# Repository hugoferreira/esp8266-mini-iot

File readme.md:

ESP8266 07/12 breakout with one Integrated Voltage Regulator (SPX3819M5-L-3-3) for 3v3 (500mA) and LEDs for Power, RX, TX and Charging.
It has a solder jump to connect GPIO16 with RST in order to enable deep sleep.
It also has an integrated LiPo charger (MCP73831), and a Mini-USB port for charging and direct programming through an integrated FTL232RL.

This is a **work in progress** so use at your own risk.

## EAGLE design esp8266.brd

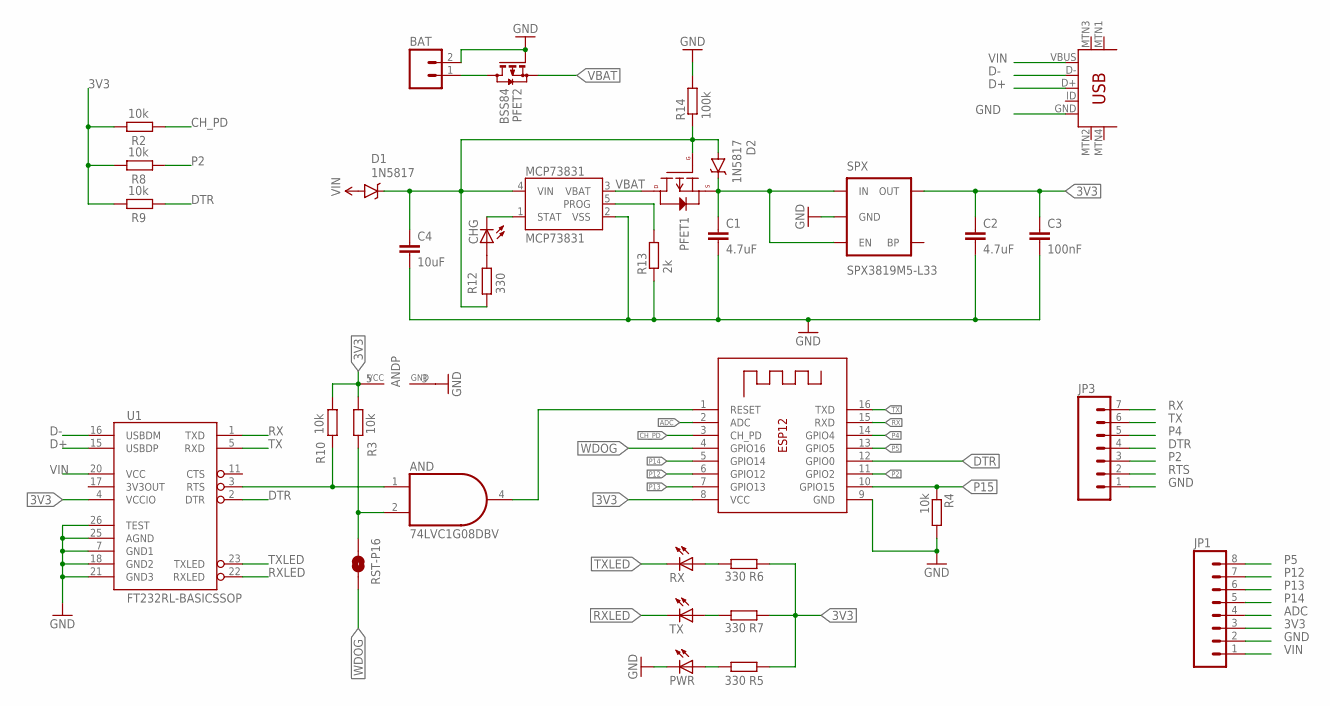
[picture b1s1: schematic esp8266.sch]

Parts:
AND: 74LVC1G08DBV; SOT23-5
BAT: M02LOCK; 1X02_LOCK
C1, C2: 4.7uF; C0805
C3: 100nF; C0805
C4: 10uF; C0805
CHG: LEDCHIPLED_0805; CHIPLED_0805
D1, D2: 1N5817; SMA-DIODE
ESP8266-07/12: ESP-12
JP1: M08LOCK; 1X08_LOCK
JP3: M07LOCK; 1X07_LOCK
MCP73831: MCP73831; SOT23-5
MINIUSB: USB-MINIB-5PIN; USB-MINIB
PFET1: P-CHANNEL-MOSFET; SOT23-3
PFET2: BSS84; SOT23
PWR: LEDCHIPLED_0805; CHIPLED_0805
R2, R3, R4, R8, R9, R10: 10k; R0805
R5, R6, R7, R12: 330; R0805
R13: 2k; R0805
R14: 100k; R0805
RST-P16: SOLDERJUMPERNO; SJ_2S-NO
RX: LEDCHIPLED_0805; CHIPLED_0805
SPX: SPX3819M5-L33; SOT23-5
TX: LEDCHIPLED_0805; CHIPLED_0805
U1: FT232RL-BASICSSOP; SSOP28DB

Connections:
3V3: AND.5 (VCC), C2.1, C3.1, ESP8266-07/12.8 (VCC), JP1.3, R2.1, R3.2, R5.2, R6.2, R7.2, R8.1, R9.1, R10.2, SPX.5 (OUT), U1.4 (VCCIO)
ADC: ESP8266-07/12.2 (ADC), JP1.4
CH_PD: ESP8266-07/12.3 (CH_PD), R2.2
D+: MINIUSB.D+, U1.15 (USBDP)
D-: MINIUSB.D-, U1.16 (USBDM)
DTR: ESP8266-07/12.12 (GPIO0), JP3.4, R9.2, U1.2 (DTR)
FTDI_RTS: AND.1 (I0), R10.1, U1.3 (RTS)
GND: AND.3 (GND), BAT.2, C1.2, C2.2, C3.2, C4.2, ESP8266-07/12.9 (GND), JP1.2, JP3.1, MCP73831.2 (VSS), MINIUSB.GND, PFET2.1 (G), PWR.C, R4.2, R13.1, R14.2, SPX.2 (GND), U1.7 (GND1), U1.18 (GND2), U1.21 (GND3), U1.25 (AGND), U1.26 (TEST)
unnamed: PWR.A, R5.1
unnamed: C4.1, D1.C, D2.A, MCP73831.4 (VIN), PFET1.1 (G), R12.1, R14.1
unnamed: CHG.A, R12.2
unnamed: AND.2 (I1), R3.1, RST-P16.1
unnamed: BAT.1, PFET2.3 (D)
unnamed: R6.1, RX.A
unnamed: R7.1, TX.A
unnamed: CHG.C, MCP73831.1 (STAT)
unnamed: MCP73831.5 (PROG), R13.2
P2: ESP8266-07/12.11 (GPIO2), JP3.3, R8.2
P4: ESP8266-07/12.14 (GPIO4), JP3.5
P5: ESP8266-07/12.13 (GPIO5), JP1.8
P12: ESP8266-07/12.6 (GPIO12), JP1.7
P13: ESP8266-07/12.7 (GPIO13), JP1.6
P14: ESP8266-07/12.5 (GPIO14), JP1.5
P15: ESP8266-07/12.10 (GPIO15), R4.1
RTS: AND.4 (O), ESP8266-07/12.1 (RESET), JP3.2
RX: ESP8266-07/12.15 (RXD), JP3.7, U1.1 (TXD)
RXLED: TX.C, U1.22 (RXLED)
TX: ESP8266-07/12.16 (TXD), JP3.6, U1.5 (RXD)
TXLED: RX.C, U1.23 (TXLED)
VBAT: MCP73831.3 (VBAT), PFET1.3 (D), PFET2.2 (S)
VIN: D1.A, JP1.1, MINIUSB.VBUS, U1.20 (VCC)
VRIN: C1.1, D2.C, PFET1.2 (S), SPX.1 (IN), SPX.3 (EN)
WDOG: ESP8266-07/12.4 (GPIO16), RST-P16.2

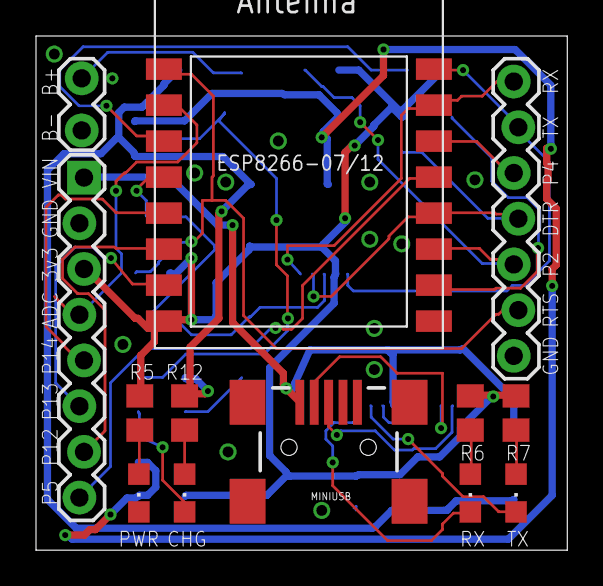
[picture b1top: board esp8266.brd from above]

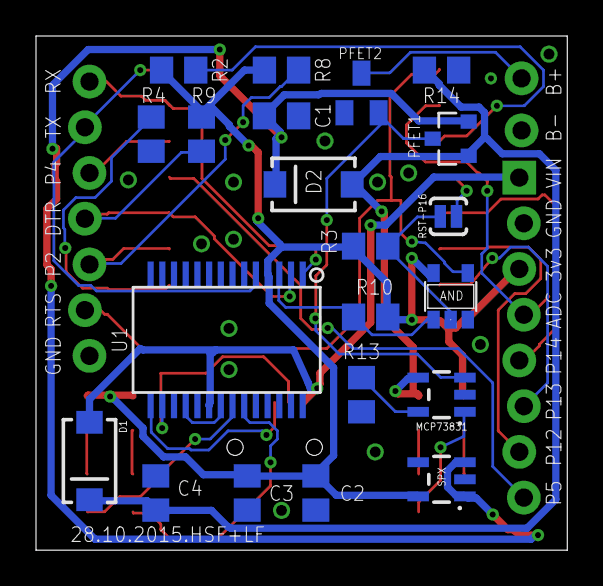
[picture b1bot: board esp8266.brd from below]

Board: 2 copper layers, 29.5 x 28.6 mm, 34 parts (21 on the bottom side), 33 nets.

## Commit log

2015-08-02 Initial commit.
2015-08-02 Added readme.
2015-08-02 Added rendered boards
2015-08-02 Added datasheets
2015-08-02 Some board updates
2015-08-05 Added BOM
2015-09-29 Minor fixes and improvements.
    Watchdog with pull ups and a AND Gate;
    Diode after VIN for satefy reasons;
    Additional VIN pin on the other side of the board for completeness;
    Switched order of pins 13 and 12;
    Small border test holes for VIN and GND.
2015-09-29 Move signature label to prevent overlap with existing via
2015-09-30 Improve labeling position
2015-09-30 Add RX and TX probes at the corners and minor style fixes
2015-10-02 Added OSHPark design rules Fixed half a dozen design rules violations (overlapping and clearance).
2015-10-02 Optimised the layout: deleted several redundant wires and at least one via.
2015-10-02 Even less wires and 3 unnecessary vias.
2015-10-02 I kinda need to stop doing this…
2015-10-23 Improve the clarity of the FDTI orientation
    This was accomplish by moving the via a to a higher position so that it doesn't interfere with the markings.
2015-10-27 Remove unnecessary components
    RTS had a capacitor that is not required per FTDI spec and is also not needed for this
    circuit. There were also 2 10k pull-ups on the RTS.
2015-10-27 Update board images
2015-10-28 Change the second VIN to ground
    It's more useful that way.
2015-10-30 New routing
2015-11-01 Finished routing
2015-11-02 Fix clearence issues
2015-11-02 More clearance adjustments and labeling improvements

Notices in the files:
parts and their libraries:
SparkFun-DiscreteSemi: Licensing: Creative Commons ShareAlike 4.0 International - https://creativecommons.org/licenses/by-sa/4.0
